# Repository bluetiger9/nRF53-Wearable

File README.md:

# Ultra-Low Power nRF53 based Health & Activity Monitor

More details on **Hackster.io**:</br>
https://www.hackster.io/bluetiger9/ultra-low-power-nrf53-based-health-activity-monitor-e023e1

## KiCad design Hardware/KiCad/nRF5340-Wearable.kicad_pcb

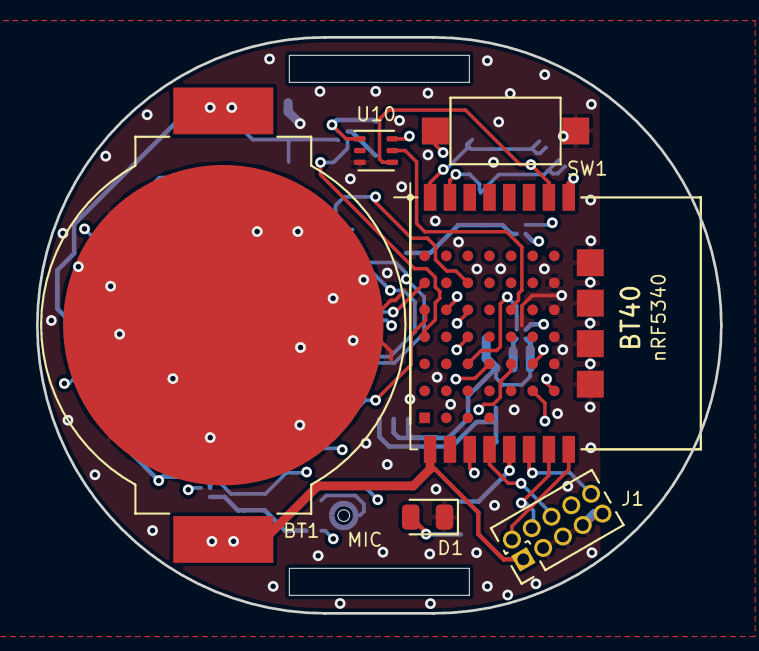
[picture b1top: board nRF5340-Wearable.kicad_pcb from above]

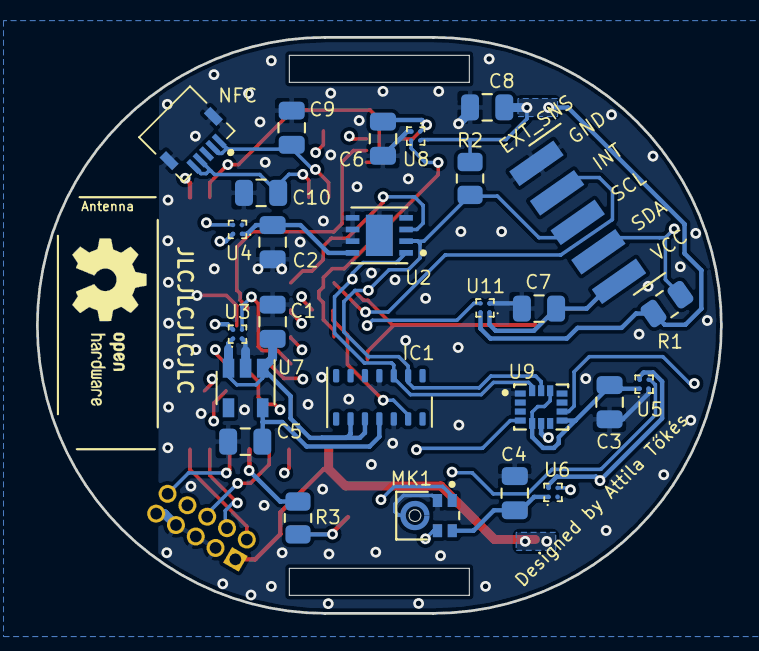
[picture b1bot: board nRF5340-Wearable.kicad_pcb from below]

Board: 4 copper layers, 38.0 x 32.0 mm, 32 parts (26 on the bottom side), 34 nets.

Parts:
BT1: CR2032; BatteryHolder_MPD_BC2003_1x2032
C1, C2, C3, C4, C5, C6, C7, C8, C9, C10: 0.1u; C_0805_2012Metric
D1: LED_Small; LED_0805_2012Metric
IC1: MAX30102; Maxim_OLGA-14_3.3x5.6mm_P0.8mm
J1: Conn_02x05_Odd_Even; PinHeader_2x05_P1.27mm_Vertical
J2: SNS_EXT; PinHeader_1x05_P2.00mm_Vertical_SMD_Pin1Left
J3: 59453-051110ECHLF; 59453051110ECHLF
MK1: ICS-41350; MIC_ICS-41350
R1, R2: 10k; R_0805_2012Metric
R3: 220; R_0805_2012Metric
SW1: SW_Push; SW_SPST_CK_RS282G05A3
U1: BT40
U2: MAX30205MTA+; SON65P300X300X80-9N
U3, U4, U5, U6, U8, U11: FPF1107; BGA4C40P2X2_84X84X60N
U7: MIC5504-1.8YM5; SOT-23-5
U9: ICM-42605; PQFN50P300X250X97-14N
U10: LTR-303ALS-01; Lite-On_LTR-303ALS-01

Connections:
+BATT: BT1.1, C8.1, J1.1, R1.1, R2.1, U1.P$9, U3.A2, U4.A2, U5.A2, U6.A2, U8.A2, U11.A2
/1.8V: C5.1, IC1.11, U7.5
/ACC_INT1: U1.P$B5, U9.4
/ACC_INT2: U1.P$B4, U9.9
/HRT_INT: IC1.13, U1.P$B6
/LIGHT_INT: U1.P$B2, U10.5
/MIC_PDM_CLK: MK1.4, U1.P$E1
/MIC_PDM_DATA: MK1.1, U1.P$E0
/NFC_1: C10.1, J3.4, J3.5, U1.P$7
/NFC_2: C9.2, J3.1, J3.2, U1.P$8
/PWR_SNS_1: U1.P$D4, U3.B2
/PWR_SNS_2: U1.P$D3, U4.B2
/PWR_SNS_3: U1.P$D2, U5.B2
/PWR_SNS_4: U1.P$D1, U6.B2
/PWR_SNS_5: U1.P$C6, U8.B2
/PWR_SNS_6: U1.P$C4, U11.B2
/RESET: J1.10, U1.P$14
/SCL: IC1.2, J2.3, R2.2, U1.P$2, U2.2, U9.13, U10.4
/SDA: IC1.3, J2.2, R1.2, U1.P$1, U2.1, U9.14, U10.6
/SNS_EXT_INT: J2.4, U1.P$A6
/SWDCLK: J1.4, U1.P$15
/SWDIO: J1.2, U1.P$16
/SWO: J1.6, U1.P$12
/TMP_OUT: U1.P$A4, U2.3
/VDD_SNS_1: C1.1, IC1.9, IC1.10, U3.A1, U7.1, U7.3
/VDD_SNS_2: C2.1, U2.8, U4.A1
/VDD_SNS_3: C3.1, U5.A1, U9.5, U9.8, U9.12
/VDD_SNS_4: C4.1, MK1.5, U6.A1
/VDD_SNS_5: C6.1, U8.A1, U10.1
/VDD_SNS_6: C7.1, J2.1, U11.A1
GND: BT1.2, C1.2, C2.2, C3.2, C4.2, C5.2, C6.2, C7.2, C8.2, C9.1, C10.2, D1.1, IC1.4, IC1.12, J1.3, J1.5, J1.7, J1.9, J2.5, J3.6, J3.7, MK1.2, MK1.3, SW1.2, U1.P$10, U1.P$A0, U1.P$B0, U1.P$C0, U1.P$D0, U1.P$F0, U1.P$F1, U1.P$F2, U1.P$F3, U2.4, U2.5, U2.6, U2.7, U2.9, U3.B1, U4.B1, U5.B1, U6.B1, U7.2, U8.B1, U9.1, U9.6, U10.3, U11.B1
unnamed: D1.2, R3.1
unnamed: R3.2, U1.P$13
unnamed: SW1.1, U1.P$11

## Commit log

2021-06-12 Add KiCAD project
2021-06-13 Add SEGGER Embedded Studio project
2021-06-13 Add 3D Files
2021-06-17 Update nRF5340 CPU App
2021-06-17 Update nRF5340 CPU Net
